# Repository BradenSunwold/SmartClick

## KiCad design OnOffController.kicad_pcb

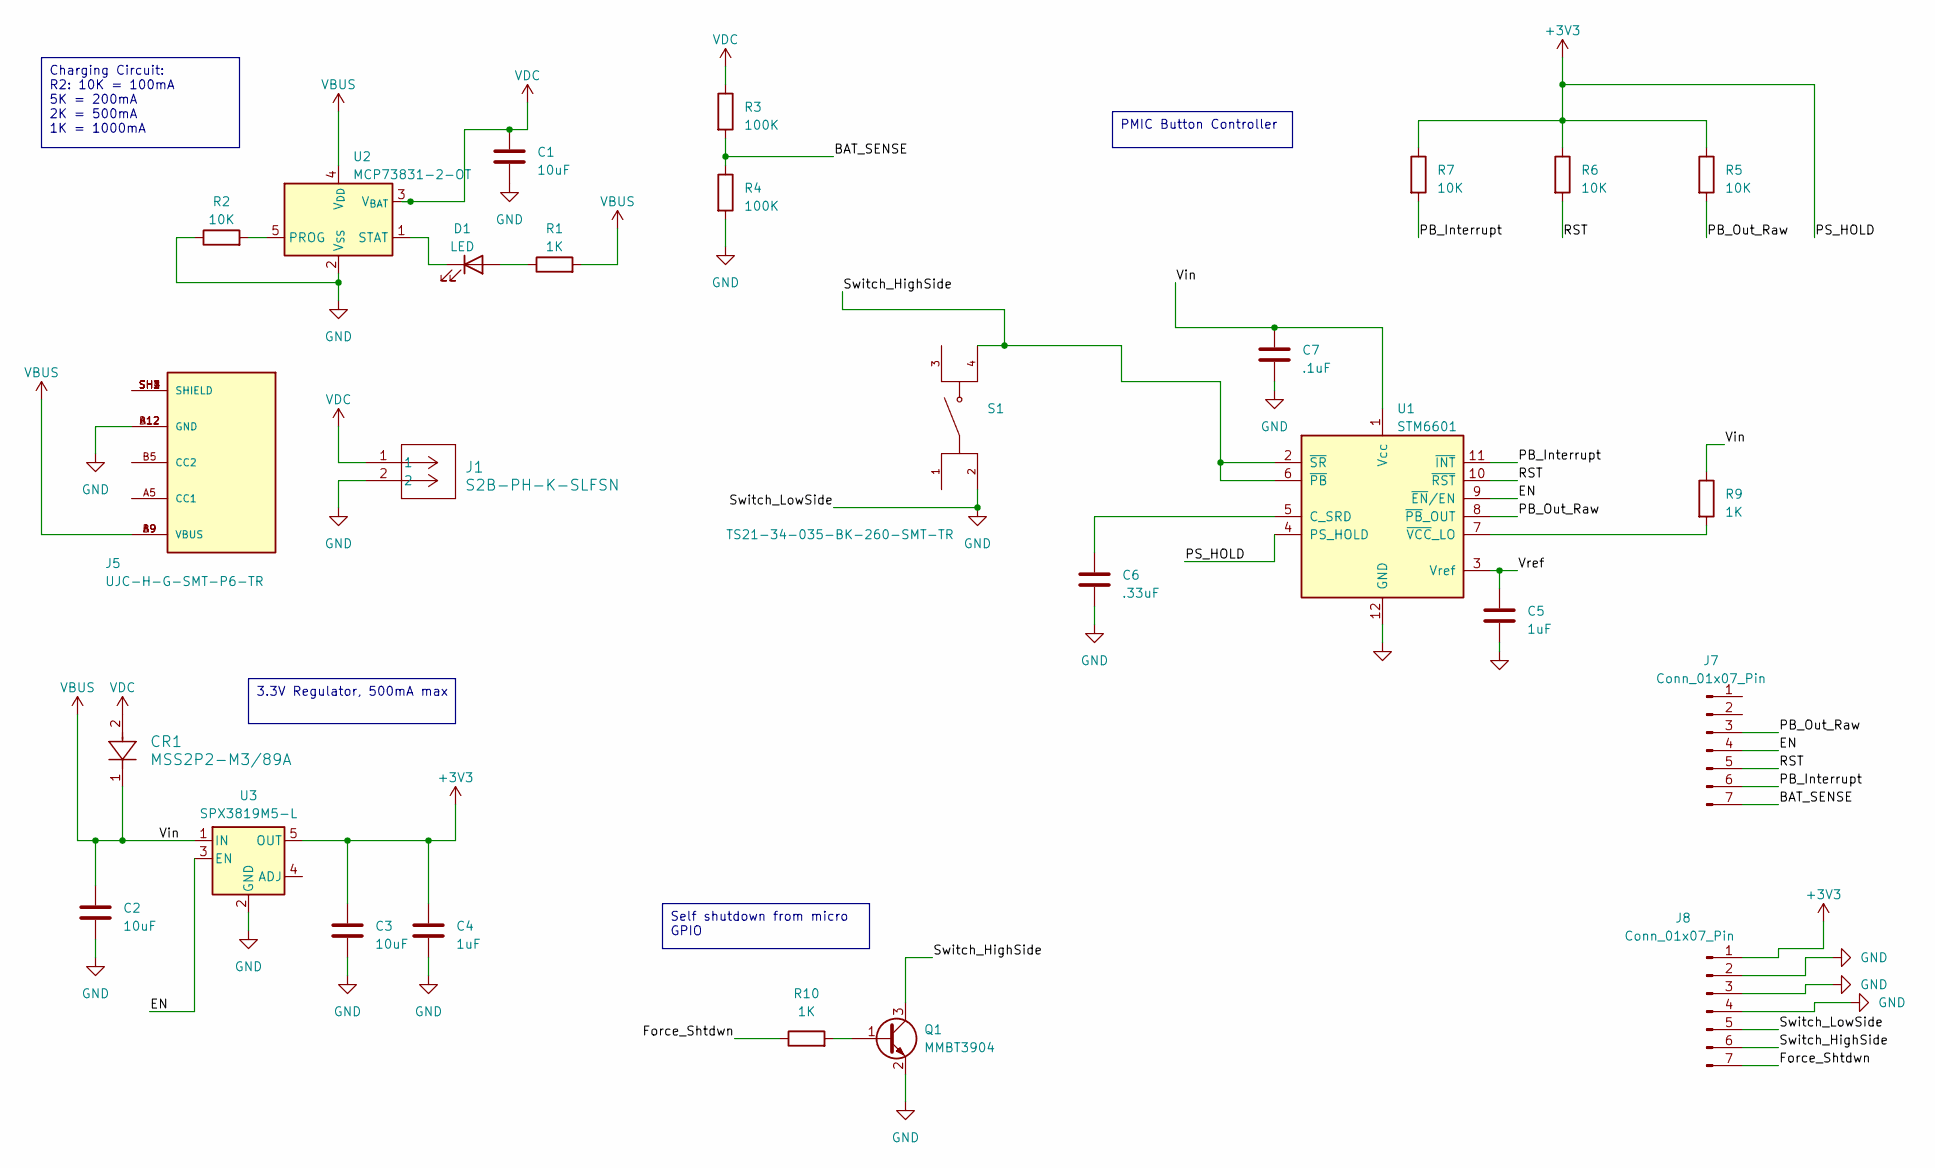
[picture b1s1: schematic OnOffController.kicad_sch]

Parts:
C1, C2, C3: 10uF; C_0402_1005Metric
C4, C5: 1uF; C_0402_1005Metric
C6: .33uF; C_0402_1005Metric
C7: .1uF; C_0402_1005Metric
CR1: MSS2P2-M3/89A; DIODE_MSP3V3
D1: LED; LED_0603_1608Metric
J1: S2B-PH-K-SLFSN; JST_PH_S2B-PH-SM4-TB_1x02-1MP_P2.00mm_Horizontal
J5: UJC-H-G-SMT-P6-TR; SAMESKY_UJC-H-G-SMT-P6-TR; PARTREV 1.0
J7, J8: Conn_01x07_Pin; qtpy_catellated_7x2
Q1: MMBT3904; SOT-23
R1, R9, R10: 1K; R_0402_1005Metric
R2, R5, R6, R7: 10K; R_0402_1005Metric
R3, R4: 100K; R_0402_1005Metric
S1: TS21-34-035-BK-260-SMT-TR; SW_TS21-34-035-BK-260-SMT-TR; PARTREV 1.01
U1: STM6601; TDFN-12_2x3mm_P0.5mm
U2: MCP73831-2-OT; SOT-23-5
U3: SPX3819M5-L; SOT-23-5

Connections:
+3V3: C3.1, C4.1, J8.1, R5.1, R6.1, R7.1, U1.4 (PS_HOLD), U3.5 (OUT)
/BAT_SENSE: J7.7, R3.2, R4.1
/EN: J7.4, U1.9 (~EN/EN), U3.3 (EN)
/Force_Shtdwn: J8.7, R10.1
/PB_Interrupt: J7.6, R7.2, U1.11 (~INT)
/PB_Out_Raw: J7.3, R5.2, U1.8 (~PB_OUT)
/RST: J7.5, R6.2, U1.10 (~RST)
/Switch_HighSide: J8.6, Q1.3 (C), S1.4, U1.2 (~SR), U1.6 (~PB)
/Vref: C5.1, U1.3 (Vref)
GND: C1.2, C2.2, C3.2, C4.2, C5.2, C6.2, C7.2, J1.2, J5.A12 (GND), J5.B12 (GND), J8.2, J8.3, J8.4, J8.5, Q1.2 (E), R2.1, R4.2, S1.2, U1.12 (GND), U2.2 (V_{SS}), U3.2 (GND)
unnamed: D1.2 (A), R1.1
unnamed: D1.1 (K), U2.1 (STAT)
unnamed: J5.SH1 (SHIELD), J5.SH2 (SHIELD), J5.SH3 (SHIELD), J5.SH4 (SHIELD)
unnamed: Q1.1 (B), R10.2
unnamed: C6.1, U1.5 (C_SRD)
unnamed: R9.2, U1.7 (~VCC_LO)
unnamed: R2.2, U2.5 (PROG)
VBUS: C2.1, C7.1, CR1.1, J5.A9 (VBUS), J5.B9 (VBUS), R1.2, R9.1, U1.1 (Vcc), U2.4 (V_{DD}), U3.1 (IN)
VDC: C1.1, CR1.2, J1.1, R3.1, U2.3 (V_{BAT})

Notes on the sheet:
PMIC Button Controller
Charging Circuit: R2: 10K = 100mA 5K = 200mA 2K = 500mA 1K = 1000mA
3.3V Regulator, 500mA max
Self shutdown from micro GPIO

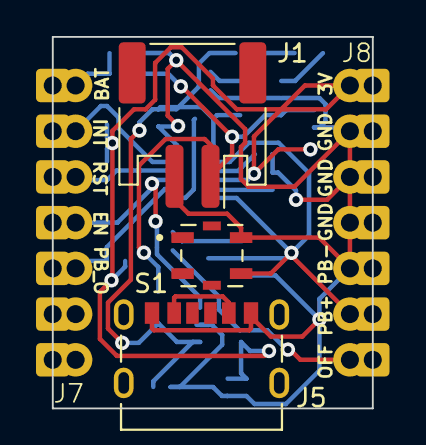
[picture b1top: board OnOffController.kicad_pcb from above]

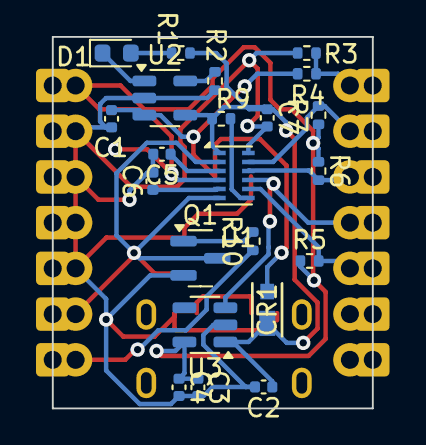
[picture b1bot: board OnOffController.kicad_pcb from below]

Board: 2 copper layers, 17.8 x 20.6 mm, 27 parts (22 on the bottom side), 19 nets.

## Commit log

2024-04-06 Finished schematic
2024-04-06 Updated USB-B and switch footprints
2024-04-06 Generated PCB files
2024-04-09 Passing DRC and added all silk screens
2024-04-10 Updated header pin spacing for 2.54mm pitch
2024-04-19 Added BOM
2025-06-13 Updated all parts to smaller package sizes and found cheaper alternatives
2025-06-16 Updated to 5V and 3.3V versions
2025-06-28 Split 3.3 and 5V into different board versions
